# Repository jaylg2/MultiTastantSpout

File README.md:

# MultiTastantSpout
This directory contains open source design materials for a rodent behavioral environment for learning from positive and negative events. These materials are for an Arduino controlled lick spout that controls delivery of small amounts of three different tastants, playing of 2 different tones (11KHz and 4KHz in this design), and timing of an in-cage light cue. 

See MultiTast_Overview for information on the build

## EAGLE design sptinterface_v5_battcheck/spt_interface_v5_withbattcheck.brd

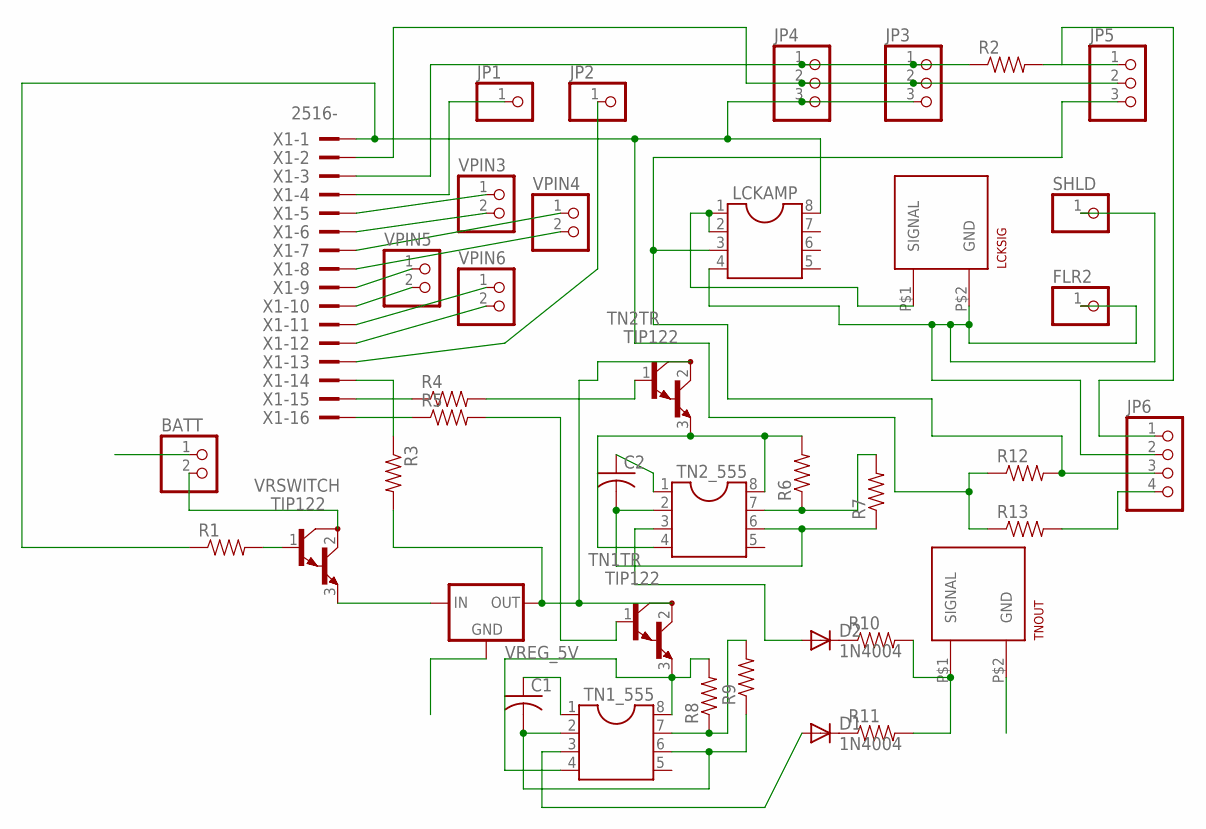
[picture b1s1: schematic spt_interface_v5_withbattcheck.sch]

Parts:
BATT: PINHD-1X2; 1X02
C1, C2: C-US050-024X044; C050-024X044
D1, D2: 1N4004; DO41-10
FLR2: PINHD-1X1; 1X01
JP1, JP2: PINHD-1X1; 1X01
JP3, JP4, JP5: PINHD-1X3; 1X03
JP6: PINHD-1X4; 1X04
LCKAMP: DIL8; DIL08
LCKSIG: BNC_VERTICAL
R1, R2, R3, R4, R5, R6, R7, R8, R9, R10, R11, R12, R13: 1KOHM-1/4W-5%(PTH)HORIZ-KIT; AXIAL-0.3EZ
SHLD: PINHD-1X1; 1X01
TN1TR, TN2TR: TIP122; TO220
TN1_555, TN2_555: DIL8; DIL08
TNOUT: BNC_VERTICAL
VPIN3, VPIN4, VPIN5, VPIN6: PINHD-1X2; 1X02
VREG_5V: 78XXL
VRSWITCH: TIP122; TO220
X1: 2516-; PAK100/2500-16

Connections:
GND: BATT.1, C1.1, C2.1, FLR2.1, JP3.2, JP4.2, JP5.2, JP6.2, LCKAMP.4, LCKSIG.P$2 (GND), SHLD.1, TN1_555.1, TN2_555.1, TNOUT.P$2 (GND), VREG_5V.GND, X1.2
unnamed: R3.P$1 (1), X1.14
unnamed: BATT.2, VRSWITCH.2 (C)
unnamed: R4.P$2 (2), TN2TR.1 (B)
unnamed: R5.P$2 (2), TN1TR.1 (B)
unnamed: R8.P$2 (2), TN1TR.3 (E), TN1_555.4, TN1_555.8
unnamed: D2.C, R10.P$1 (1)
unnamed: R4.P$1 (1), X1.15
unnamed: JP3.3, JP4.3, LCKAMP.8, R1.P$1 (1), R12.P$1 (1), R13.P$1 (1), X1.1
unnamed: D1.A, TN1_555.3
unnamed: LCKAMP.1, LCKAMP.2, LCKSIG.P$1 (SIGNAL)
unnamed: R6.P$1 (1), R7.P$2 (2), TN2_555.7
unnamed: R8.P$1 (1), R9.P$2 (2), TN1_555.7
unnamed: C2.2, R7.P$1 (1), TN2_555.2, TN2_555.6
unnamed: C1.2, R9.P$1 (1), TN1_555.2, TN1_555.6
unnamed: D2.A, TN2_555.3
unnamed: VPIN5.1, X1.9
unnamed: R10.P$2 (2), R11.P$2 (2), TNOUT.P$1 (SIGNAL)
unnamed: JP3.1, JP4.1, R2.P$1 (1), X1.3
unnamed: JP5.1, JP6.1, R2.P$2 (2)
unnamed: VPIN3.1, X1.5
unnamed: VPIN3.2, X1.6
unnamed: VPIN4.1, X1.7
unnamed: VPIN4.2, X1.8
unnamed: VPIN5.2, X1.10
unnamed: VPIN6.1, X1.11
unnamed: VPIN6.2, X1.12
unnamed: R6.P$2 (2), TN2TR.3 (E), TN2_555.4, TN2_555.8
unnamed: JP5.3, JP6.3, LCKAMP.3, R12.P$2 (2)
unnamed: VREG_5V.IN, VRSWITCH.3 (E)
unnamed: JP1.1, X1.4
unnamed: JP2.1, X1.13
unnamed: R1.P$2 (2), VRSWITCH.1 (B)
unnamed: D1.C, R11.P$1 (1)
unnamed: R5.P$1 (1), X1.16
unnamed: R3.P$2 (2), TN1TR.2 (C), TN2TR.2 (C), VREG_5V.OUT
unnamed: JP6.4, R13.P$2 (2)

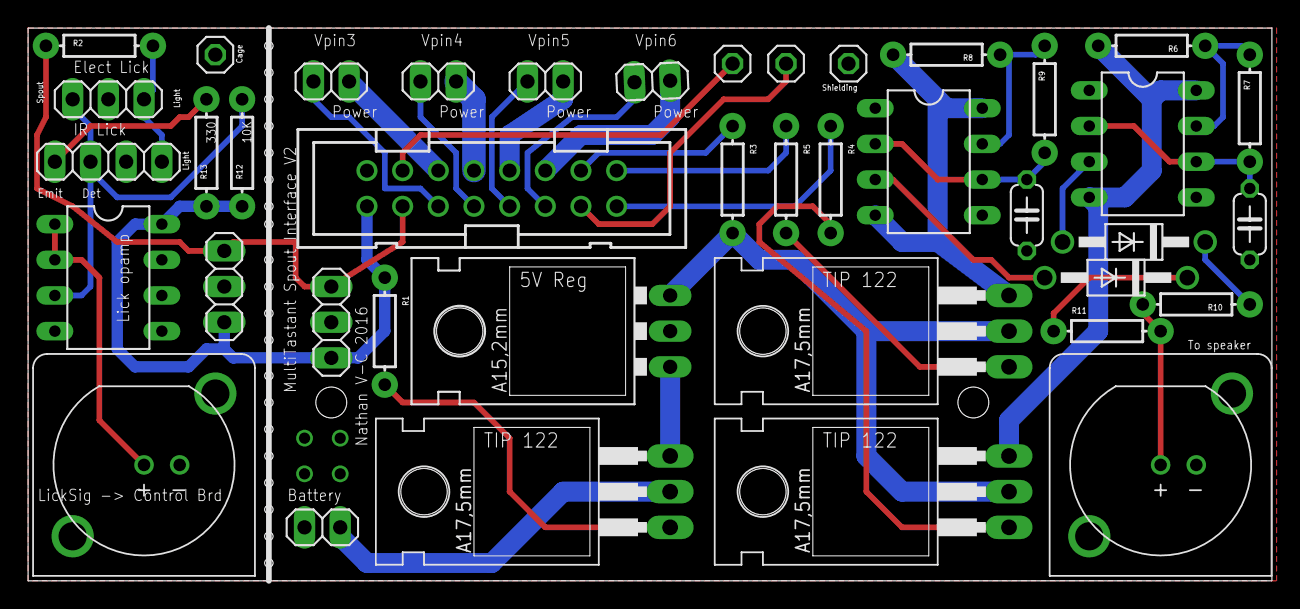
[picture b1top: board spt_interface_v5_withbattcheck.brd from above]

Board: 2 copper layers, 88.6 x 39.4 mm, 40 parts (0 on the bottom side), 37 nets.

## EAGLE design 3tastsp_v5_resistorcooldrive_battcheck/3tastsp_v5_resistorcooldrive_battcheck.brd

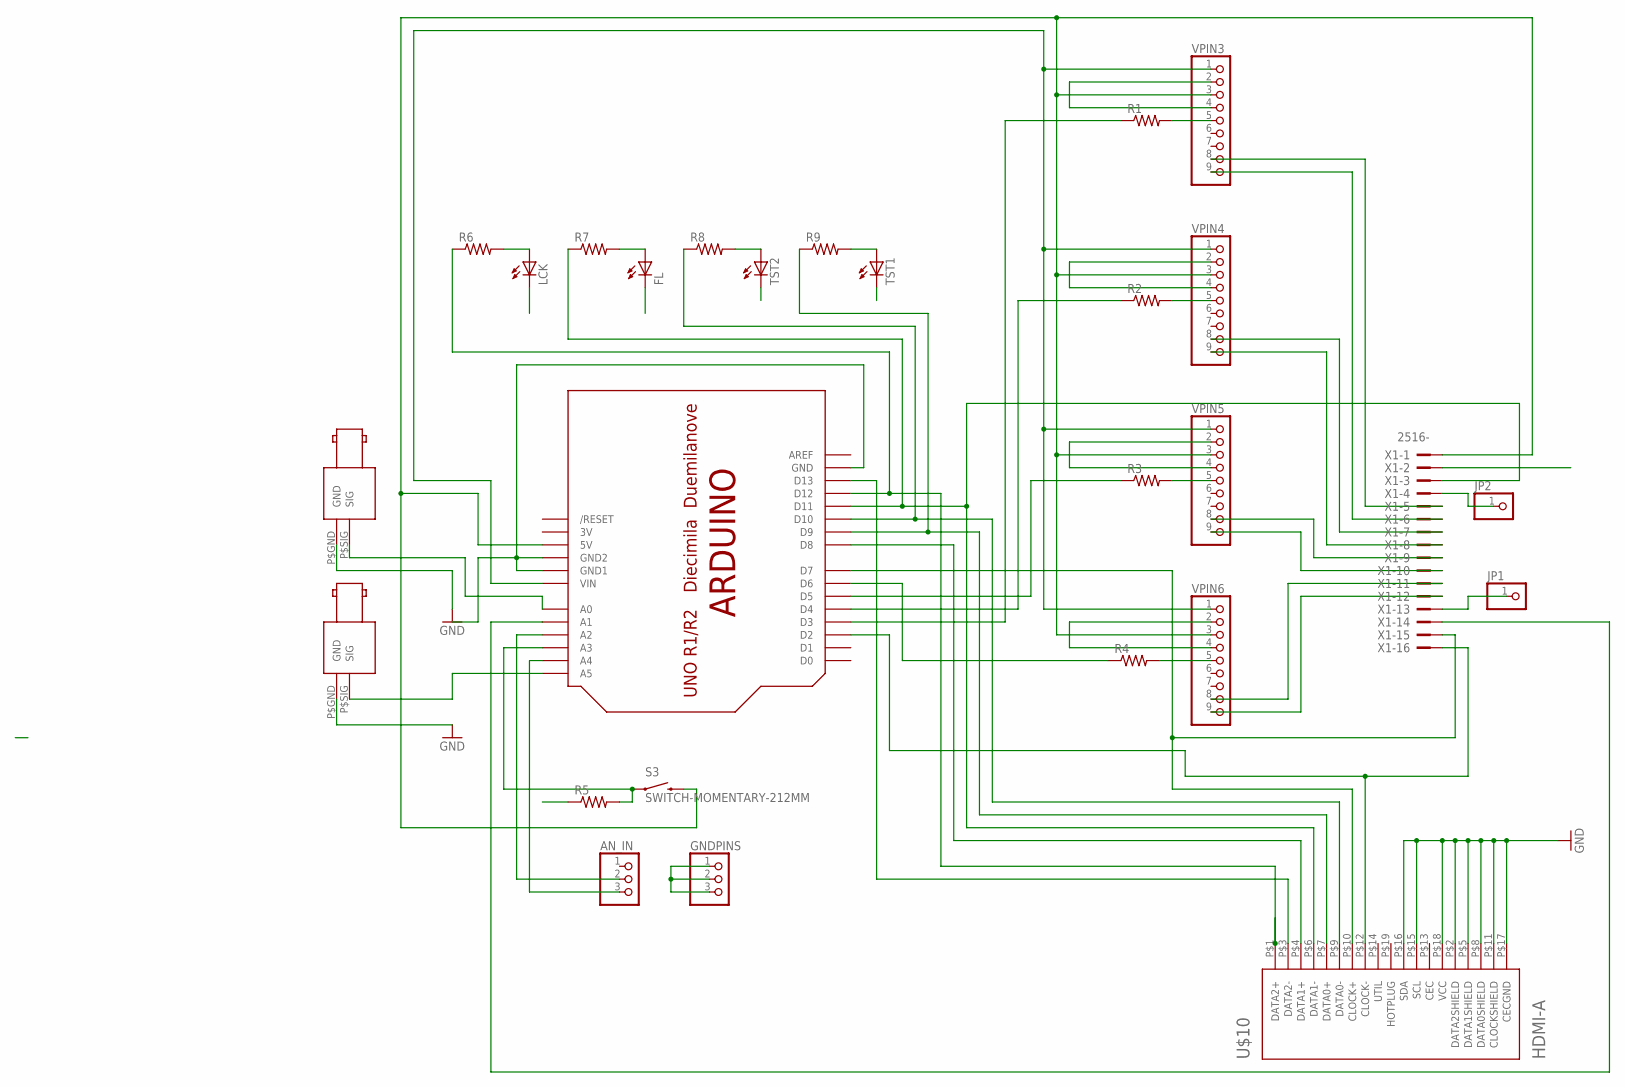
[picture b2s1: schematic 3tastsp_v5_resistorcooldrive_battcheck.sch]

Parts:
AN_IN: PINHD-1X3; 1X03
FL: LED5MM
GNDPINS: PINHD-1X3; 1X03
JP1, JP2: PINHD-1X1; 1X01
LCK: LED5MM
LICKSIG: BNC_RIGHT_ANGLE
R1, R2, R3, R4, R5, R6, R7, R8, R9: 1KOHM-1/4W-1%(PTH)HORIZ-KIT; AXIAL-0.3EZ
S3: SWITCH-MOMENTARY-212MM; TACTILE-PTH-12MM
TRIALSIG: BNC_RIGHT_ANGLE
TST1, TST2: LED5MM
U$1: ARDUINO-NOHOLE
U$10: HDMI-A; HDMI_A
VPIN3, VPIN4, VPIN5, VPIN6: PINHD-1X9; 1X09
X1: 2516-; PAK100/2500-16

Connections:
3V: U$1.3V
D6: U$1.D13, U$10.P$3 (DATA2-)
D7: R6.P$1 (1), U$1.D12, U$10.P$1 (DATA2+)
D8: U$1.D8, U$10.P$4 (DATA1+)
D9: R7.P$1 (1), U$1.D11, U$10.P$6 (DATA1-), X1.3
D10: R9.P$1 (1), U$1.D9, U$10.P$7 (DATA0+)
D11: R8.P$1 (1), U$1.D10, U$10.P$9 (DATA0-)
D12: U$1.D7, U$10.P$10 (CLOCK+), X1.15
D13: U$1.D2, U$10.P$12 (CLOCK-), X1.16
GND: FL.K (C), GNDPINS.1, GNDPINS.2, GNDPINS.3, LCK.K (C), LICKSIG.P$GND (GND), R5.P$1 (1), TRIALSIG.P$GND (GND), TST1.K (C), TST2.K (C), U$1.GND, U$1.GND1, U$1.GND2, U$10.P$2 (DATA2SHIELD), U$10.P$5 (DATA1SHIELD), U$10.P$8 (DATA0SHIELD), U$10.P$11 (CLOCKSHIELD), U$10.P$15 (SCL), U$10.P$16 (SDA), U$10.P$17 (CECGND), U$10.P$18 (VCC), VPIN3.2, VPIN3.4, VPIN4.2, VPIN4.4, VPIN5.2, VPIN5.4, VPIN6.2, VPIN6.4, X1.2
unnamed: S3.3 (2), U$1.5V, VPIN3.3, VPIN4.3, VPIN5.3, VPIN6.3, X1.1
unnamed: TRIALSIG.P$SIG (SIG), U$1.A5
unnamed: LICKSIG.P$SIG (SIG), U$1.A0
unnamed: LCK.A, R6.P$2 (2)
unnamed: FL.A, R7.P$2 (2)
unnamed: R8.P$2 (2), TST2.A
unnamed: R9.P$2 (2), TST1.A
unnamed: R1.P$2 (2), VPIN3.5
unnamed: AN_IN.3, U$1.A4
unnamed: AN_IN.2, U$1.A2
unnamed: R2.P$2 (2), VPIN4.5
unnamed: R4.P$1 (1), U$1.D6
unnamed: R3.P$1 (1), U$1.D5
unnamed: R2.P$1 (1), U$1.D4
unnamed: R1.P$1 (1), U$1.D3
unnamed: JP2.1, X1.4
unnamed: R5.P$2 (2), S3.1, U$1.A3
unnamed: U$1.VIN, VPIN3.1, VPIN4.1, VPIN5.1, VPIN6.1
unnamed: VPIN3.8, X1.5
unnamed: VPIN3.9, X1.6
unnamed: VPIN4.8, X1.7
unnamed: VPIN4.9, X1.8
unnamed: VPIN5.9, X1.10
unnamed: VPIN5.8, X1.9
unnamed: VPIN6.8, X1.11
unnamed: VPIN6.9, X1.12
unnamed: R3.P$2 (2), VPIN5.5
unnamed: R4.P$2 (2), VPIN6.5
unnamed: U$1.A1, X1.14
unnamed: JP1.1, X1.13

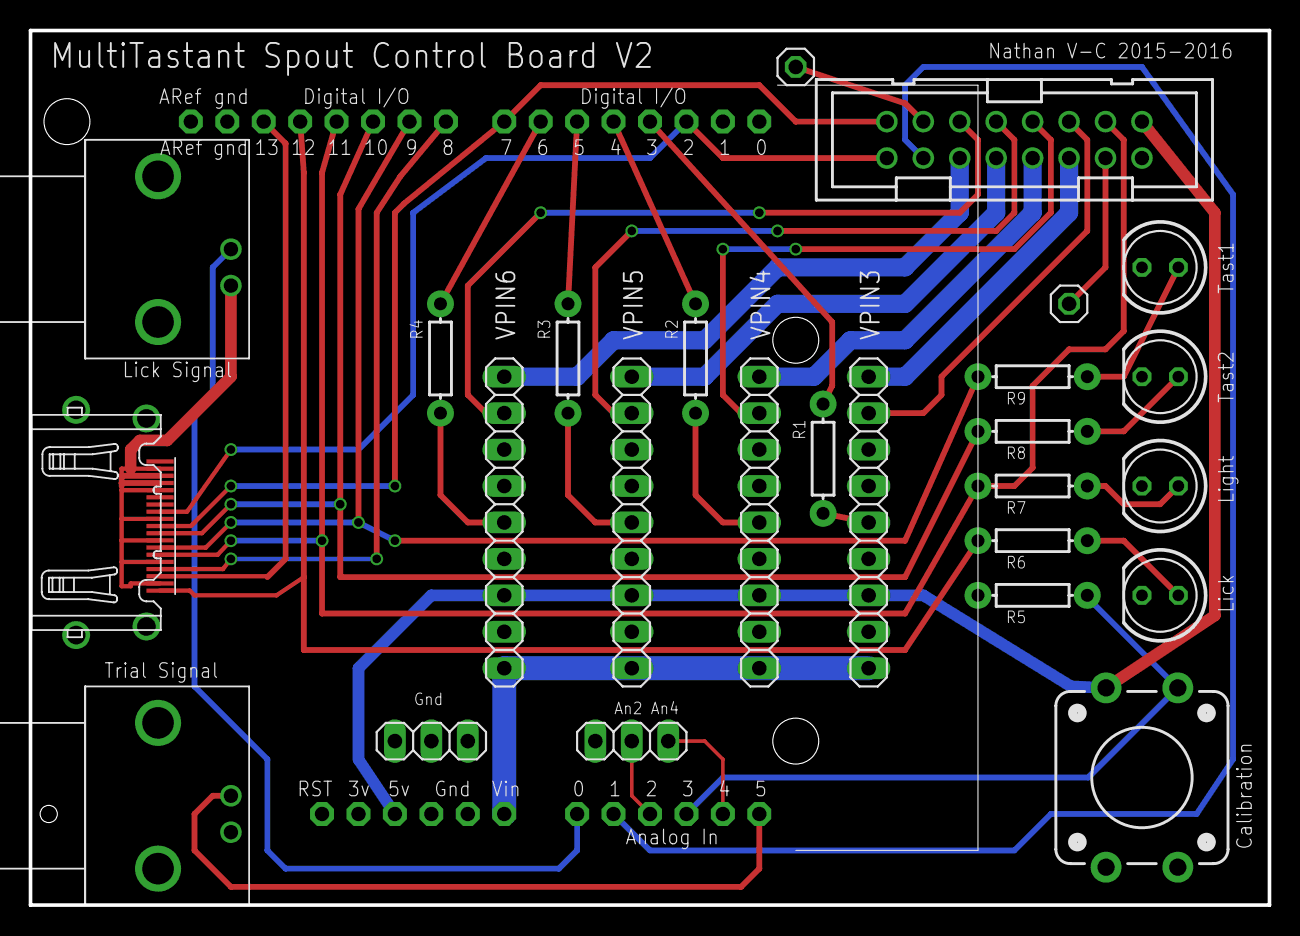
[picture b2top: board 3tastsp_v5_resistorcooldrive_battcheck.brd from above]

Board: 2 copper layers, 86.4 x 61.0 mm, 27 parts (0 on the bottom side), 39 nets.

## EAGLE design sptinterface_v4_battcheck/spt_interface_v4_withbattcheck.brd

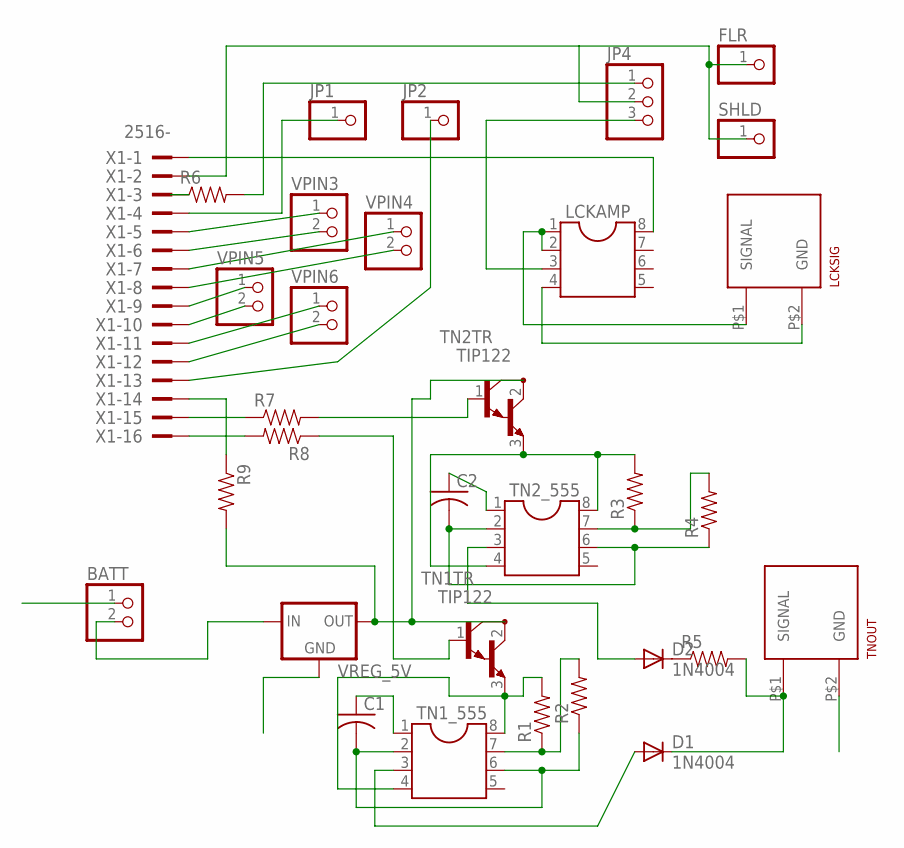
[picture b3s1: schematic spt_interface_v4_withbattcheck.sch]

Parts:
BATT: PINHD-1X2; 1X02
C1, C2: C-US050-024X044; C050-024X044
D1, D2: 1N4004; DO41-10
FLR: PINHD-1X1; 1X01
JP1, JP2: PINHD-1X1; 1X01
JP4: PINHD-1X3; 1X03
LCKAMP: DIL8; DIL08
LCKSIG: BNC_VERTICAL
R1, R2, R3, R4, R5, R6, R7, R8, R9: RESISTORPTH-1/2W; AXIAL-0.5
SHLD: PINHD-1X1; 1X01
TN1TR, TN2TR: TIP122; TO220
TN1_555, TN2_555: DIL8; DIL08
TNOUT: BNC_VERTICAL
VPIN3, VPIN4, VPIN5, VPIN6: PINHD-1X2; 1X02
VREG_5V: 78XXL
X1: 2516-; PAK100/2500-16

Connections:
GND: BATT.1, C1.1, C2.1, FLR.1, JP4.2, LCKAMP.4, LCKSIG.P$2 (GND), SHLD.1, TN1_555.1, TN2_555.1, TNOUT.P$2 (GND), VREG_5V.GND, X1.2
unnamed: R9.P$1 (1), X1.14
unnamed: BATT.2, VREG_5V.IN
unnamed: R7.P$2 (2), TN2TR.1 (B)
unnamed: R8.P$1 (1), TN1TR.1 (B)
unnamed: R1.P$2 (2), TN1TR.3 (E), TN1_555.4, TN1_555.8
unnamed: D2.C, R5.P$1 (1)
unnamed: R7.P$1 (1), X1.15
unnamed: LCKAMP.8, X1.1
unnamed: D1.A, TN1_555.3
unnamed: LCKAMP.1, LCKAMP.2, LCKSIG.P$1 (SIGNAL)
unnamed: R3.P$1 (1), R4.P$2 (2), TN2_555.7
unnamed: R1.P$1 (1), R2.P$2 (2), TN1_555.7
unnamed: C2.2, R4.P$1 (1), TN2_555.2, TN2_555.6
unnamed: C1.2, R2.P$1 (1), TN1_555.2, TN1_555.6
unnamed: D2.A, TN2_555.3
unnamed: VPIN5.1, X1.9
unnamed: D1.C, R5.P$2 (2), TNOUT.P$1 (SIGNAL)
unnamed: JP4.1, R6.P$2 (2)
unnamed: R6.P$1 (1), X1.3
unnamed: VPIN3.1, X1.5
unnamed: VPIN3.2, X1.6
unnamed: VPIN4.1, X1.7
unnamed: VPIN4.2, X1.8
unnamed: VPIN5.2, X1.10
unnamed: VPIN6.1, X1.11
unnamed: VPIN6.2, X1.12
unnamed: R3.P$2 (2), TN2TR.3 (E), TN2_555.4, TN2_555.8
unnamed: JP4.3, LCKAMP.3
unnamed: JP1.1, X1.4
unnamed: JP2.1, X1.13
unnamed: R8.P$2 (2), X1.16
unnamed: R9.P$2 (2), TN1TR.2 (C), TN2TR.2 (C), VREG_5V.OUT

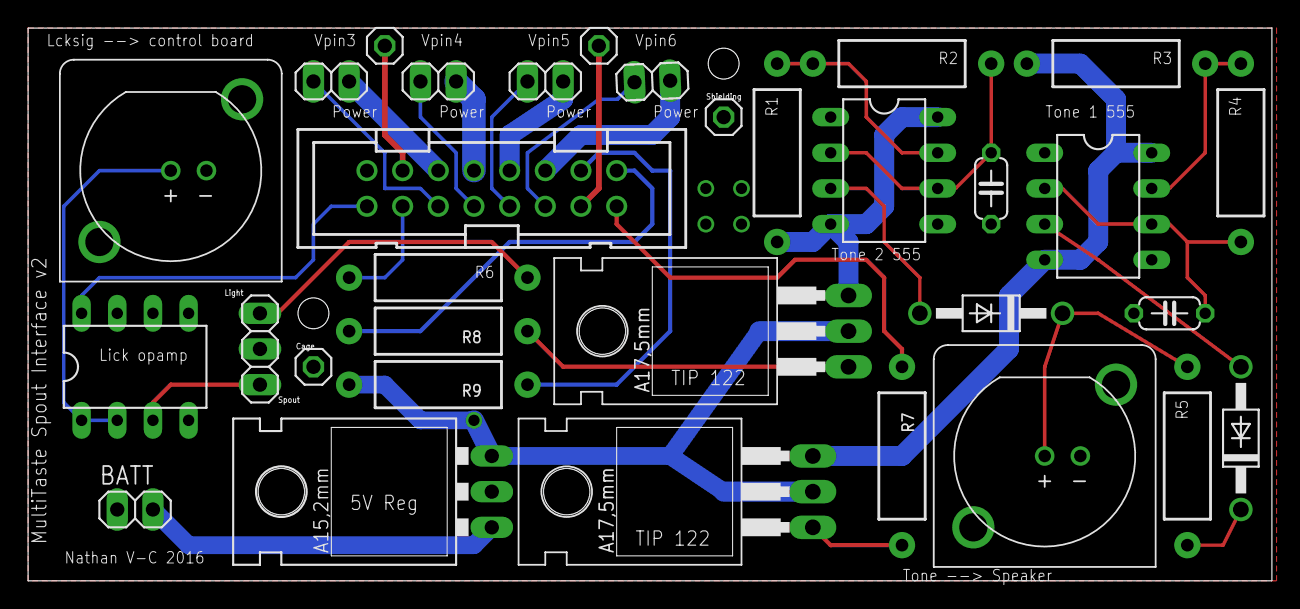
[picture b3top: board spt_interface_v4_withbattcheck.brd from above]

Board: 2 copper layers, 88.6 x 39.4 mm, 32 parts (0 on the bottom side), 33 nets.

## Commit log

2016-05-03 Update PCBs, add IR option
2016-05-28 add parts list, update arduino with pin assignment for new PCBs

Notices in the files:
parts and their libraries:
SparkFun-Resistors: Licensing: Creative Commons ShareAlike 4.0 International - https://creativecommons.org/licenses/by-sa/4.0
